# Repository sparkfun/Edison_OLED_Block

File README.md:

*Fork of SparkFun Edison OLED Block repo, adding a command-line tool to interact with the OLED Block*

See [Firmware/oled](Firmware/oled/) for the command-line tool.

Contains very minor modifications to the original SparkFun OLED drivers, such as making the screen buffer a public field of the `edOLED` class rather than a private static.

-----

SparkFun Edison OLED Block
===========================

[*SparkFun Edison OLED Block(DEV-13035)*](https://www.sparkfun.com/products/13035)

Equip your Edison with a graphic display using the Edison OLED board! This board features a 0.66", 64x48 pixel monochrome OLED.

To add some control over your Edison and the OLED, this board also includes a small joystick and a pair of push-buttons. Use them to create a game, file navigator, or more!

Repository Contents
-------------------
* **/Firmware** - Example Pong sketch to demonstrate OLED Functionality. 
* **/Hardware** - All Eagle design files (.brd, .sch)
* **/Production** - Test bed files and production panel files

Documentation
--------------
* **[Hookup Guide](https://learn.sparkfun.com/tutorials/sparkfun-blocks-for-intel-edison---oled-block)** - Basic hookup guide for the OLED Block.
* **[SparkFun Fritzing repo](https://github.com/sparkfun/Fritzing_Parts)** - Fritzing diagrams for SparkFun products.
* **[SparkFun 3D Model repo](https://github.com/sparkfun/3D_Models)** - 3D models of SparkFun products. 
* **[SparkFun Graphical Datasheets](https://github.com/sparkfun/Graphical_Datasheets)** -Graphical Datasheets for various SparkFun products.

License Information
-------------------

This product is _**open source**_! 

Please review the LICENSE.md file for license information. 

If you have any questions or concerns on licensing, please contact techsupport@sparkfun.com.

Distributed as-is; no warranty is given.

- Your friends at SparkFun.

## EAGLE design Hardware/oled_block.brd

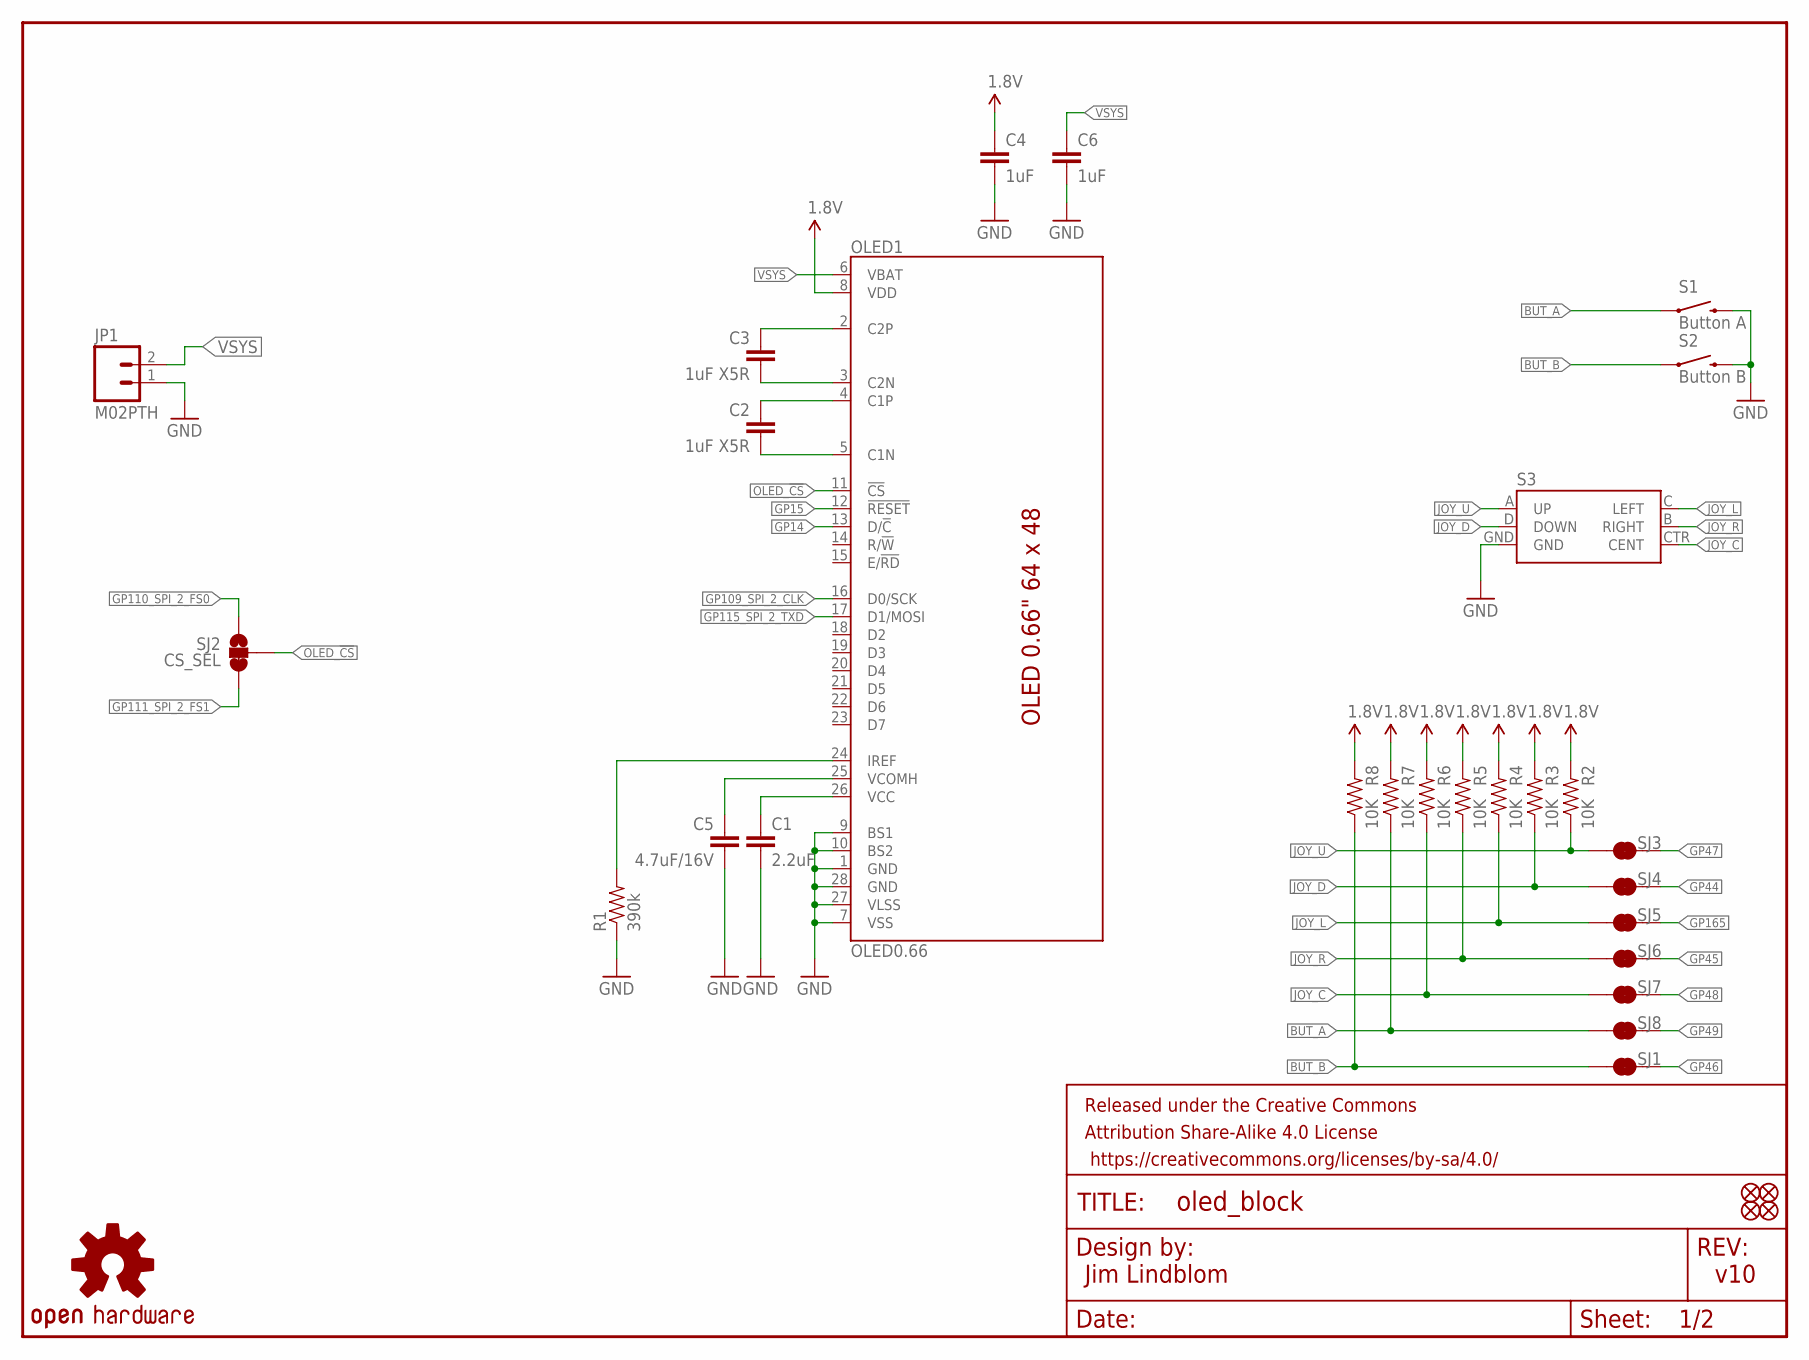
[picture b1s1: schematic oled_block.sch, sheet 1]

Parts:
C1: 2.2uF; 0805
C2, C3: 1uF X5R; 0805
C4, C6: 1uF; 0603-CAP
C5: 4.7uF/16V; 1206
FID1, FID2, FID3, FID4: FIDUCIAL1X2; FIDUCIAL-1X2
FRAME1: FRAME-LETTER; CREATIVE_COMMONS
JP1: M02PTH; 1X02
LOGO2: OSHW-LOGOS; OSHW-LOGO-S
OLED1: OLED0.66; OLED-0.66-64X48
R1: 390k; 0603-RES
R2, R3, R4, R5, R6, R7, R8: 10K; 0603-RES
S1: Button A; TACTILE_SWITCH_TALL
S2: Button B; TACTILE_SWITCH_TALL
S3: JOYSTICK_MINI
SJ1, SJ3, SJ4, SJ5, SJ6, SJ7, SJ8: JUMPER-PAD-2-NC_BY_TRACE; PAD-JUMPER-2-NC_BY_TRACE_YES_SILK
SJ2: CS_SEL; PAD-JUMPER-3-2OF3_NC_BY_TRACE_YES_SILK_FULL_BOX

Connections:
1.8V: C4.1, OLED1.8 (VDD), R2.2, R3.2, R4.2, R5.2, R6.2, R7.2, R8.2; also elsewhere on the board
BUT_A: R7.1, S1.A2 (1), SJ8.1
BUT_B: R8.1, S2.A2 (1), SJ1.1
C1N: C2.2, OLED1.5 (C1N)
C1P: C2.1, OLED1.4 (C1P)
C2N: C3.2, OLED1.3 (C2N)
C2P: C3.1, OLED1.2 (C2P)
GND: C1.2, C4.2, C5.2, C6.2, JP1.1, OLED1.1 (GND), OLED1.7 (VSS), OLED1.9 (BS1), OLED1.10 (BS2), OLED1.27 (VLSS), OLED1.28 (GND), R1.1, S1.B2 (2), S2.B2 (2), S3.GND; also elsewhere on the board
GP14: OLED1.13 (D/!C!); also elsewhere on the board
GP15: OLED1.12 (!RESET!); also elsewhere on the board
GP44: SJ4.2; also elsewhere on the board
GP45: SJ6.2; also elsewhere on the board
GP46: SJ1.2; also elsewhere on the board
GP47: SJ3.2; also elsewhere on the board
GP48: SJ7.2; also elsewhere on the board
GP49: SJ8.2; also elsewhere on the board
GP109_SPI_2_CLK: OLED1.16 (D0/SCK); also elsewhere on the board
GP110_SPI_2_FS0: SJ2.1; also elsewhere on the board
GP111_SPI_2_FS1: SJ2.3; also elsewhere on the board
GP115_SPI_2_TXD: OLED1.17 (D1/MOSI); also elsewhere on the board
GP165: SJ5.2; also elsewhere on the board
IREF: OLED1.24 (IREF), R1.2
JOY_C: R6.1, S3.CTR (CENT), SJ7.1
JOY_D: R3.1, S3.D (DOWN), SJ4.1
JOY_L: R4.1, S3.C (LEFT), SJ5.1
JOY_R: R5.1, S3.B (RIGHT), SJ6.1
JOY_U: R2.1, S3.A (UP), SJ3.1
OLED_!CS!: OLED1.11 (!CS!), SJ2.2
VCC: C1.1, OLED1.26 (VCC)
VCOMH: C5.1, OLED1.25 (VCOMH)
VSYS: C6.1, JP1.2, OLED1.6 (VBAT); also elsewhere on the board

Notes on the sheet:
Jim Lindblom
v10

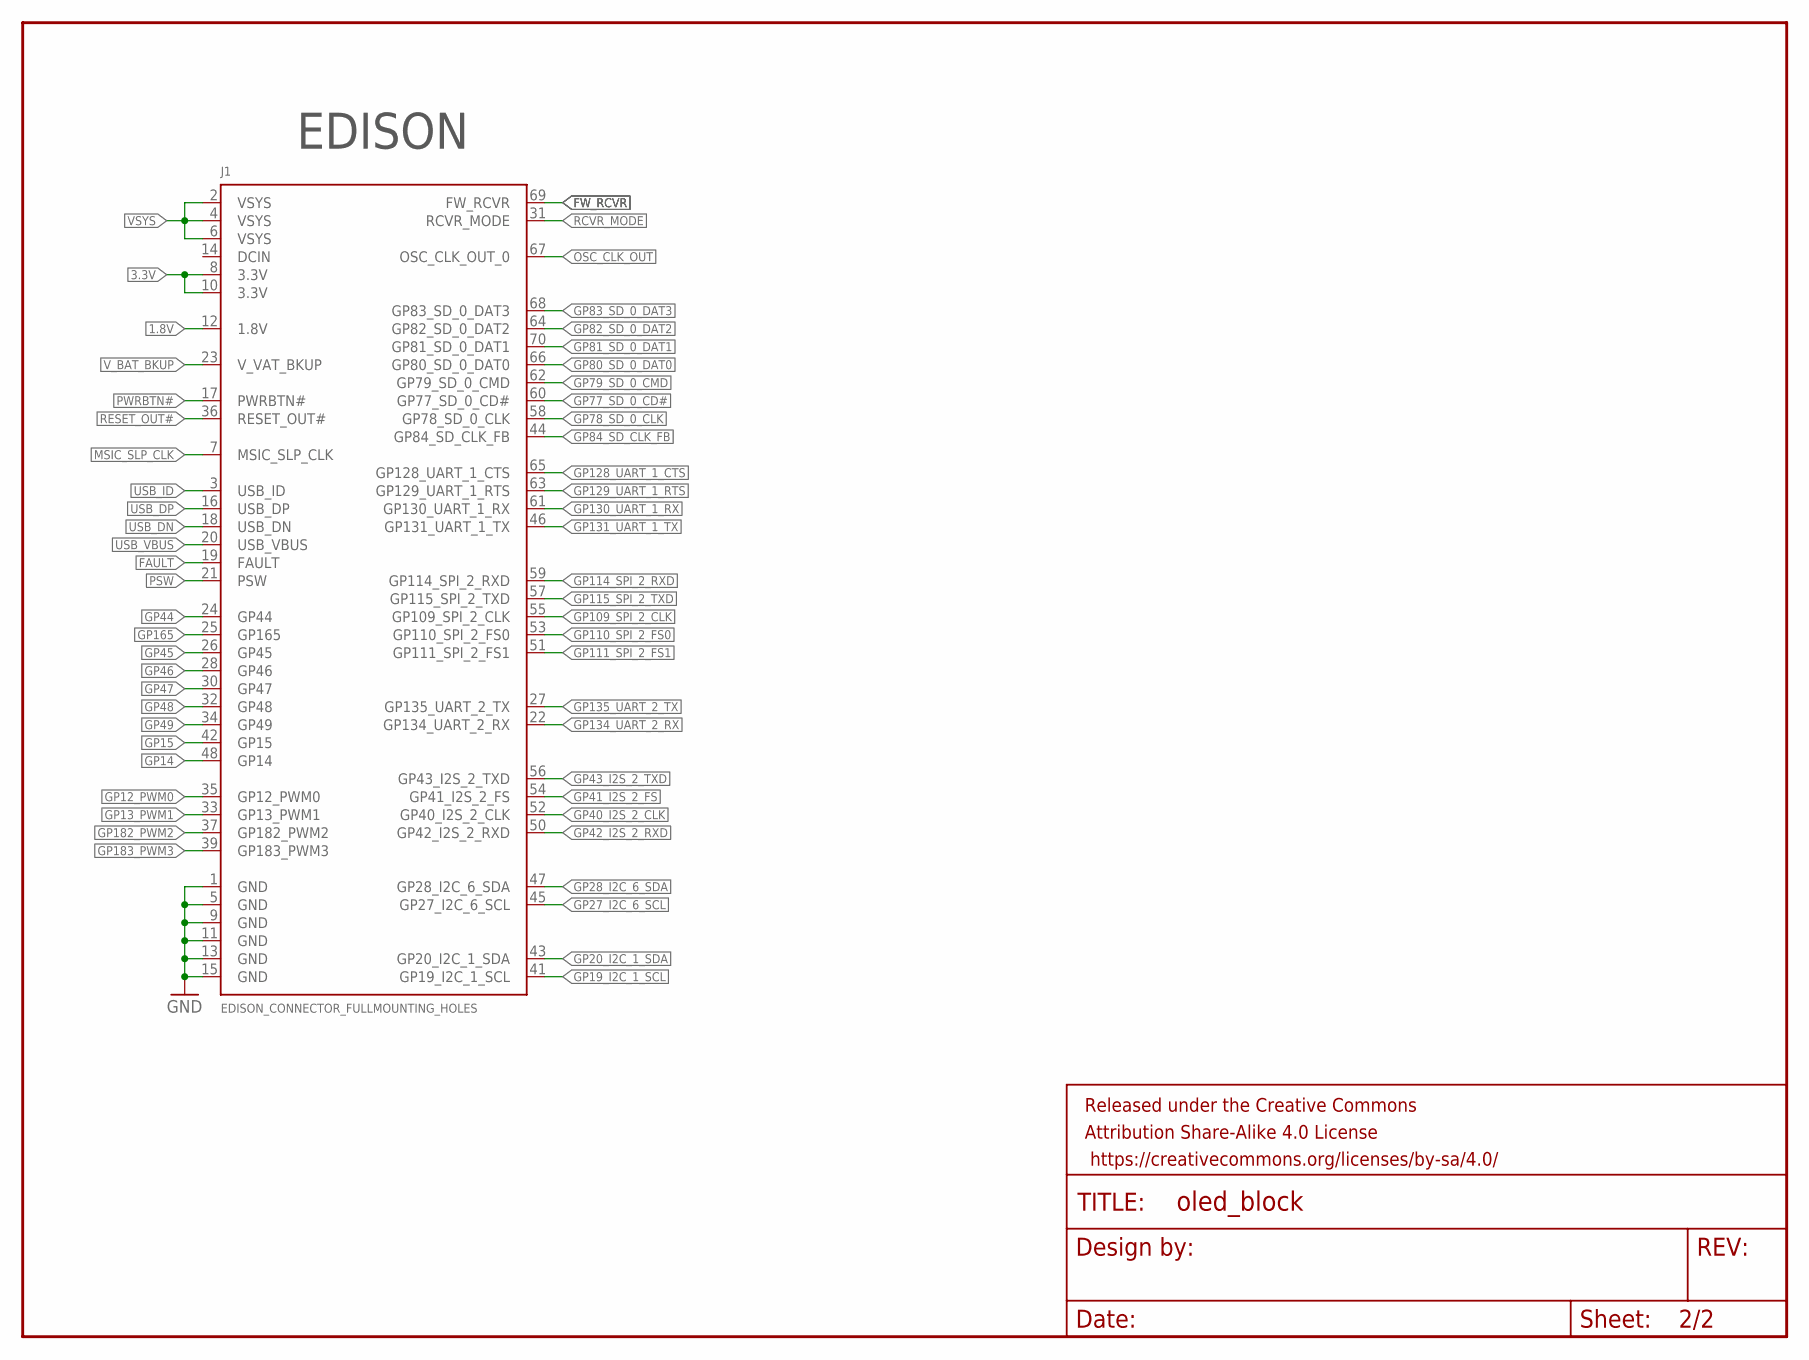
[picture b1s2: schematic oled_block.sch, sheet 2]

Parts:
FRAME2: FRAME-LETTER; CREATIVE_COMMONS
J1: EDISON_CONNECTOR_FULLMOUNTING_HOLES; EDISON_DAUGHTER

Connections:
1.8V: J1.12 (1.8V); also elsewhere on the board
3.3V: J1.8 (3.3V), J1.10 (3.3V)
FAULT: J1.19 (FAULT)
FW_RCVR: J1.69 (FW_RCVR)
GND: J1.1 (GND), J1.5 (GND), J1.9 (GND), J1.11 (GND), J1.13 (GND), J1.15 (GND); also elsewhere on the board
GP12_PWM0: J1.35 (GP12_PWM0)
GP13_PWM1: J1.33 (GP13_PWM1)
GP14: J1.48 (GP14); also elsewhere on the board
GP15: J1.42 (GP15); also elsewhere on the board
GP19_I2C_1_SCL: J1.41 (GP19_I2C_1_SCL)
GP20_I2C_1_SDA: J1.43 (GP20_I2C_1_SDA)
GP27_I2C_6_SCL: J1.45 (GP27_I2C_6_SCL)
GP28_I2C_6_SDA: J1.47 (GP28_I2C_6_SDA)
GP40_I2S_2_CLK: J1.52 (GP40_I2S_2_CLK)
GP41_I2S_2_FS: J1.54 (GP41_I2S_2_FS)
GP42_I2S_2_RXD: J1.50 (GP42_I2S_2_RXD)
GP43_I2S_2_TXD: J1.56 (GP43_I2S_2_TXD)
GP44: J1.24 (GP44); also elsewhere on the board
GP45: J1.26 (GP45); also elsewhere on the board
GP46: J1.28 (GP46); also elsewhere on the board
GP47: J1.30 (GP47); also elsewhere on the board
GP48: J1.32 (GP48); also elsewhere on the board
GP49: J1.34 (GP49); also elsewhere on the board
GP77_SD_0_CD#: J1.60 (GP77_SD_0_CD#)
GP78_SD_0_CLK: J1.58 (GP78_SD_0_CLK)
GP79_SD_0_CMD: J1.62 (GP79_SD_0_CMD)
GP80_SD_0_DAT0: J1.66 (GP80_SD_0_DAT0)
GP81_SD_0_DAT1: J1.70 (GP81_SD_0_DAT1)
GP82_SD_0_DAT2: J1.64 (GP82_SD_0_DAT2)
GP83_SD_0_DAT3: J1.68 (GP83_SD_0_DAT3)
GP84_SD_CLK_FB: J1.44 (GP84_SD_CLK_FB)
GP109_SPI_2_CLK: J1.55 (GP109_SPI_2_CLK); also elsewhere on the board
GP110_SPI_2_FS0: J1.53 (GP110_SPI_2_FS0); also elsewhere on the board
GP111_SPI_2_FS1: J1.51 (GP111_SPI_2_FS1); also elsewhere on the board
GP114_SPI_2_RXD: J1.59 (GP114_SPI_2_RXD)
GP115_SPI_2_TXD: J1.57 (GP115_SPI_2_TXD); also elsewhere on the board
GP128_UART_1_CTS: J1.65 (GP128_UART_1_CTS)
GP129_UART_1_RTS: J1.63 (GP129_UART_1_RTS)
GP130_UART_1_RX: J1.61 (GP130_UART_1_RX)
GP131_UART_1_TX: J1.46 (GP131_UART_1_TX)
GP134_UART_2_RX: J1.22 (GP134_UART_2_RX)
GP135_UART_2_TX: J1.27 (GP135_UART_2_TX)
GP165: J1.25 (GP165); also elsewhere on the board
GP182_PWM2: J1.37 (GP182_PWM2)
GP183_PWM3: J1.39 (GP183_PWM3)
MSIC_SLP_CLK: J1.7 (MSIC_SLP_CLK)
OSC_CLK_OUT: J1.67 (OSC_CLK_OUT_0)
PSW: J1.21 (PSW)
PWRBTN#: J1.17 (PWRBTN#)
RCVR_MODE: J1.31 (RCVR_MODE)
RESET_OUT#: J1.36 (RESET_OUT#)
USB_DN: J1.18 (USB_DN)
USB_DP: J1.16 (USB_DP)
USB_ID: J1.3 (USB_ID)
USB_VBUS: J1.20 (USB_VBUS)
VSYS: J1.2 (VSYS), J1.4 (VSYS), J1.6 (VSYS); also elsewhere on the board
V_BAT_BKUP: J1.23 (V_VAT_BKUP)

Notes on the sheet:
EDISON

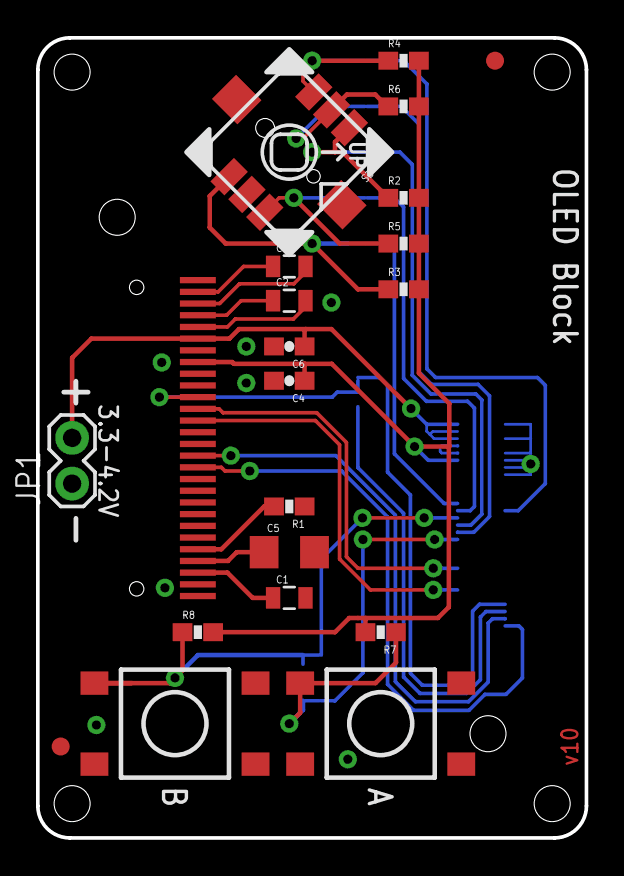
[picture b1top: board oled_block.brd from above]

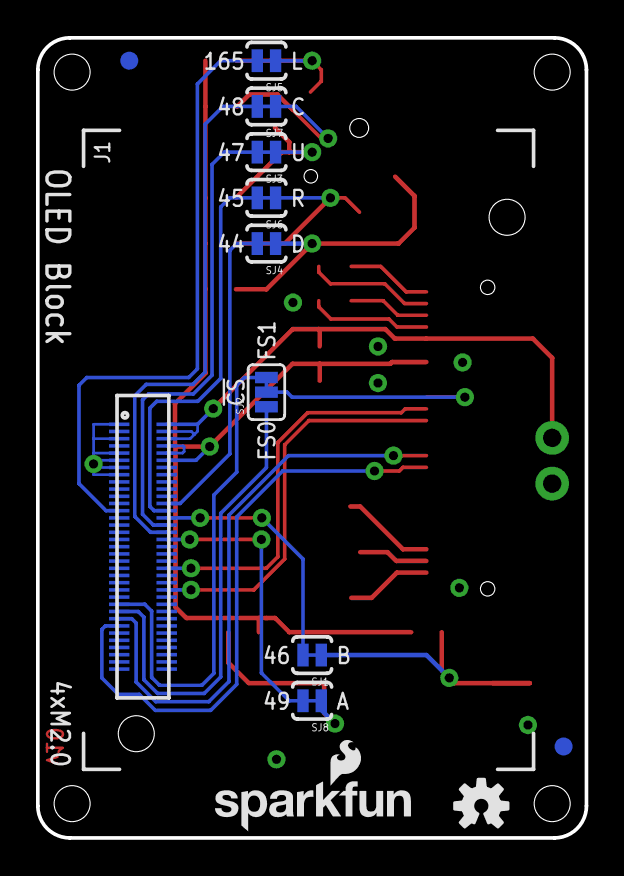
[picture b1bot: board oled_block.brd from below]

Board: 2 copper layers, 30.5 x 44.5 mm, 36 parts (13 on the bottom side), 32 nets.

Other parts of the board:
LOGO3: SFE_LOGO_NAME_FLAME.1_INCH; SFE_LOGO_NAME_FLAME_.1

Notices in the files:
parts and their libraries:
SparkFun-Aesthetics: Licensing: Creative Commons ShareAlike 4.0 International - https://creativecommons.org/licenses/by-sa/4.0
SparkFun-Aesthetics: Released under the Creative Commons Attribution Share-Alike 4.0 License
SparkFun-Aesthetics: https://creativecommons.org/licenses/by-sa/4.0
